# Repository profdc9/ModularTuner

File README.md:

This a project to create a Modular Antenna Tuner System that can be reconfigured for
different needs.  This material is copyrighted by Daniel Marks (KW4TI) and licensed under
the Creative Commons License CC-BY-SA 4.0.

This project is a toolkit for making automatic antenna tuners and smart HF antennas.

A description and documentation of this project may be found in the "doc" directory as
ModularTuner-Guide.pdf.

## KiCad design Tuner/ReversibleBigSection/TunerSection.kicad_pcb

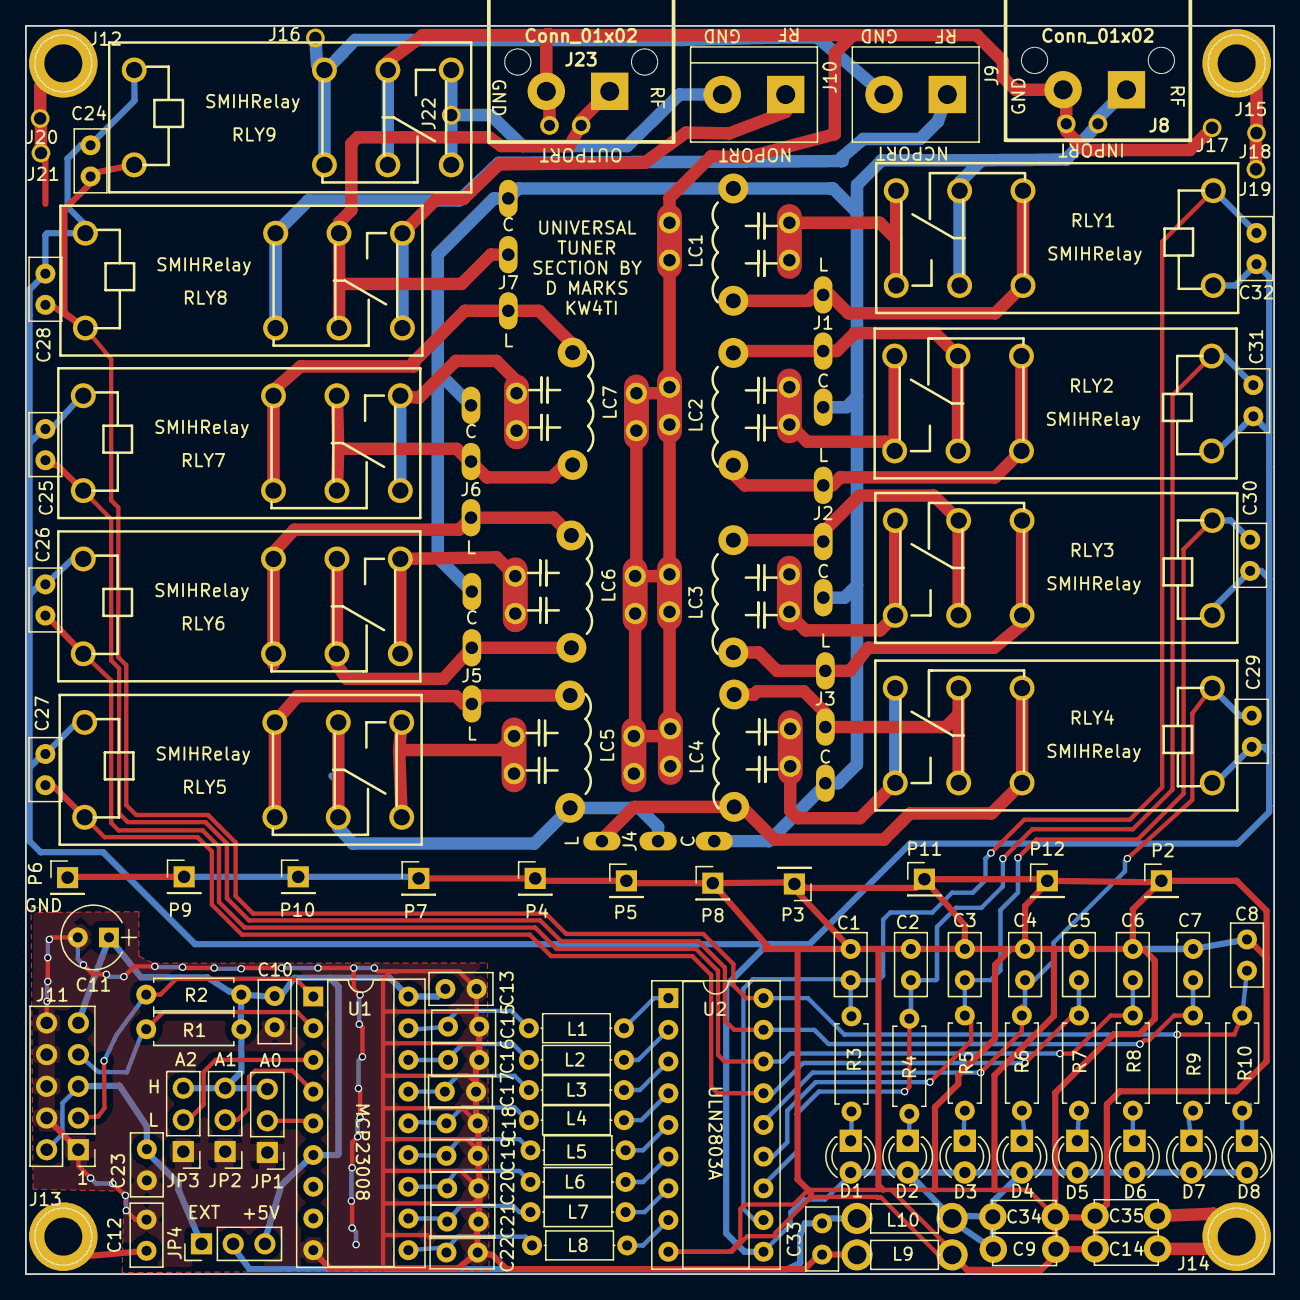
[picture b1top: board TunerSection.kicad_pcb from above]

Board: 2 copper layers, 100.0 x 100.0 mm, 119 parts (0 on the bottom side), 74 nets.

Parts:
C1, C2, C3, C4, C5, C6, C7, C8, C12, C15, C18, C19, C20, C21, C24, C25, C26, C27, C28, C29, C30, C31, C32: 10 nF; C_Disc_D5.0mm_W2.5mm_P2.50mm
C9, C14, C34, C35: 10 nF; C_Disc_D5.0mm_W2.5mm_P5.00mm
C10, C13, C23, C33: 100 nF; C_Disc_D5.0mm_W2.5mm_P2.50mm
C11: 100 uF; CP_Radial_Tantal_D5.0mm_P2.50mm
C16, C17: C_Small; C_Disc_D5.0mm_W2.5mm_P2.50mm
C22: 10 nFl; C_Disc_D5.0mm_W2.5mm_P2.50mm
D1, D2, D3, D4, D5, D6, D7, D8: LED; LED_D3.0mm
J1, J2, J3, J4, J5, J6, J7: Conn_01x03; ThreeJumperPt
J8, J23: Conn_01x02; bnc_90_1-1337543-0_pad_combo
J9, J10: Conn_01x02; TerminalBlock_bornier-2_P5.08mm
J11: Conn_02x05_Odd_Even; Pin_Header_Straight_2x05_Pitch2.54mm
J12, J13, J14, J15: Conn_01x01; 1pin
J16, J17, J18, J19, J20, J21, J22: Conn_01x01; SOLDERJUMPER
JP1, JP2, JP3, JP4: Jumper_NC_Dual; Pin_Header_Straight_1x03_Pitch2.54mm
L1, L2, L3, L4, L5, L6, L7, L8, L9, L10: 100 uH; L_Axial_L5.3mm_D2.2mm_P7.62mm_Horizontal_Vishay_IM-1
LC1, LC2, LC3, LC4, LC5, LC6, LC7: CAPIND; MultiCAPIND
P2, P3, P4, P5, P6, P7, P8, P9, P10, P11, P12: Conn_01x01; Pin_Header_Straight_1x01_Pitch2.54mm
R1, R2: 2.2k; R_Axial_DIN0207_L6.3mm_D2.5mm_P7.62mm_Horizontal
R3, R4, R5, R6, R7, R8, R9, R10: 1k; R_Axial_DIN0207_L6.3mm_D2.5mm_P7.62mm_Horizontal
RLY1, RLY2, RLY3, RLY4, RLY5, RLY6, RLY7, RLY8, RLY9: SPDTRelay; SMIHRelay
U1: MCP23008; DIP-18_W7.62mm_Socket
U2: ULN2803A; DIP-18_W7.62mm_Socket

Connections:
+5V: C10.2, C11.1, C13.2, J11.9, JP1.3, JP2.3, JP3.3, JP4.3, R1.1, R2.1, U1.6, U1.18
EXTPWR: C33.2, JP4.2, L10.1
GND: C10.1, C11.2, C12.2, C13.1, C15.2, C16.2, C17.2, C18.2, C19.2, C20.2, C21.2, C22.2, C23.1, C33.1, J11.1, J11.4, J11.6, J11.8, J11.10, JP1.1, JP2.1, JP3.1, L9.1, U1.9
unnamed: C12.1, J13.1
unnamed: C14.1, C35.1, J14.1
unnamed: C15.1, L1.1, U1.17
unnamed: C16.1, L2.1, U1.16
unnamed: C17.1, L3.1, U1.15
unnamed: C18.1, L4.1, U1.14
unnamed: C19.1, L5.1, U1.13
unnamed: C20.1, L6.1, U1.12
unnamed: C21.1, L7.1, U1.11
unnamed: C22.1, L8.1, U1.10
unnamed: C23.2, J11.2, J11.5, JP4.1
unnamed: D1.1, R3.1
unnamed: D2.1, R4.1
unnamed: D3.1, R5.1
unnamed: D4.1, R6.1
unnamed: D5.1, R7.1
unnamed: D6.1, R8.1
unnamed: D7.1, R9.1
unnamed: D8.1, R10.1
unnamed: J1.1, LC1.3, RLY1.2
unnamed: J1.2, LC2.4, RLY2.1
unnamed: J2.1, LC2.3, RLY2.2
unnamed: J2.2, LC3.4, RLY3.1
unnamed: J3.1, LC3.3, RLY3.2
unnamed: J3.2, LC4.4, RLY4.1
unnamed: J4.1, LC4.3, RLY4.2
unnamed: J4.2, LC5.4, RLY5.1
unnamed: J5.1, LC5.3, RLY5.2
unnamed: J5.2, LC6.4, RLY6.1
unnamed: J6.1, LC6.3, RLY6.2
unnamed: J6.2, LC7.4, RLY7.1
unnamed: J7.1, LC7.3, RLY7.2
unnamed: J9.1, RLY8.2
unnamed: J10.1, RLY8.3
unnamed: J10.2, J22.1, RLY9.3
unnamed: J12.1, J20.1, J21.1
unnamed: J15.1, J18.1, J19.1
unnamed: J9.2, J16.1, RLY9.2
unnamed: J7.2, J23.1, RLY8.1
unnamed: JP1.2, U1.5
unnamed: JP2.2, U1.4
unnamed: JP3.2, U1.3
unnamed: L1.2, U2.1
unnamed: L2.2, U2.2
unnamed: L3.2, U2.3
unnamed: L4.2, U2.4
unnamed: L5.2, U2.5
unnamed: L6.2, U2.6
unnamed: L7.2, U2.7
unnamed: L8.2, U2.8
unnamed: LC1.1, RLY1.3
unnamed: LC2.1, RLY2.3
unnamed: LC3.1, RLY3.3
unnamed: LC4.1, RLY4.3
unnamed: LC5.1, RLY5.3
unnamed: LC6.1, RLY6.3
unnamed: LC7.1, RLY7.3
RFGND: J8.2, J17.1, J23.2, LC1.2, LC2.2, LC3.2, LC4.2, LC5.2, LC6.2, LC7.2, RLY9.1
RFPORT1: J1.3, J2.3, J3.3, J4.3, J5.3, J6.3, J7.3, J8.1, LC1.4, RLY1.1
RLY1: C1.2, C32.2, R3.2, RLY1.5, U2.11
RLY2: C2.2, C31.2, R4.2, RLY2.5, U2.12
RLY3: C3.2, C30.2, R5.2, RLY3.5, U2.13
RLY4: C4.2, C29.2, R6.2, RLY4.5, U2.14
RLY5: C5.2, C27.2, R7.2, RLY5.5, U2.15
RLY6: C6.2, C26.2, R8.2, RLY6.5, U2.16
RLY7: C7.2, C25.2, R9.2, RLY7.5, U2.17
RLY8: C8.2, C24.2, C28.2, R10.2, RLY8.5, RLY9.5, U2.18
RLYGND: C1.1, C2.1, C3.1, C4.1, C5.1, C6.1, C7.1, C8.1, C9.2, C14.2, C34.2, C35.2, L9.2, P2.1, P3.1, P4.1, P5.1, P6.1, P7.1, P8.1, P9.1, P10.1, P11.1, P12.1, U2.9
RLYPWR: C9.1, C24.1, C25.1, C26.1, C27.1, C28.1, C29.1, C30.1, C31.1, C32.1, C34.1, D1.2, D2.2, D3.2, D4.2, D5.2, D6.2, D7.2, D8.2, L10.2, RLY1.4, RLY2.4, RLY3.4, RLY4.4, RLY5.4, RLY6.4, RLY7.4, RLY8.4, RLY9.4, U2.10
SCL: J11.3, R2.2, U1.1
SDA: J11.7, R1.2, U1.2

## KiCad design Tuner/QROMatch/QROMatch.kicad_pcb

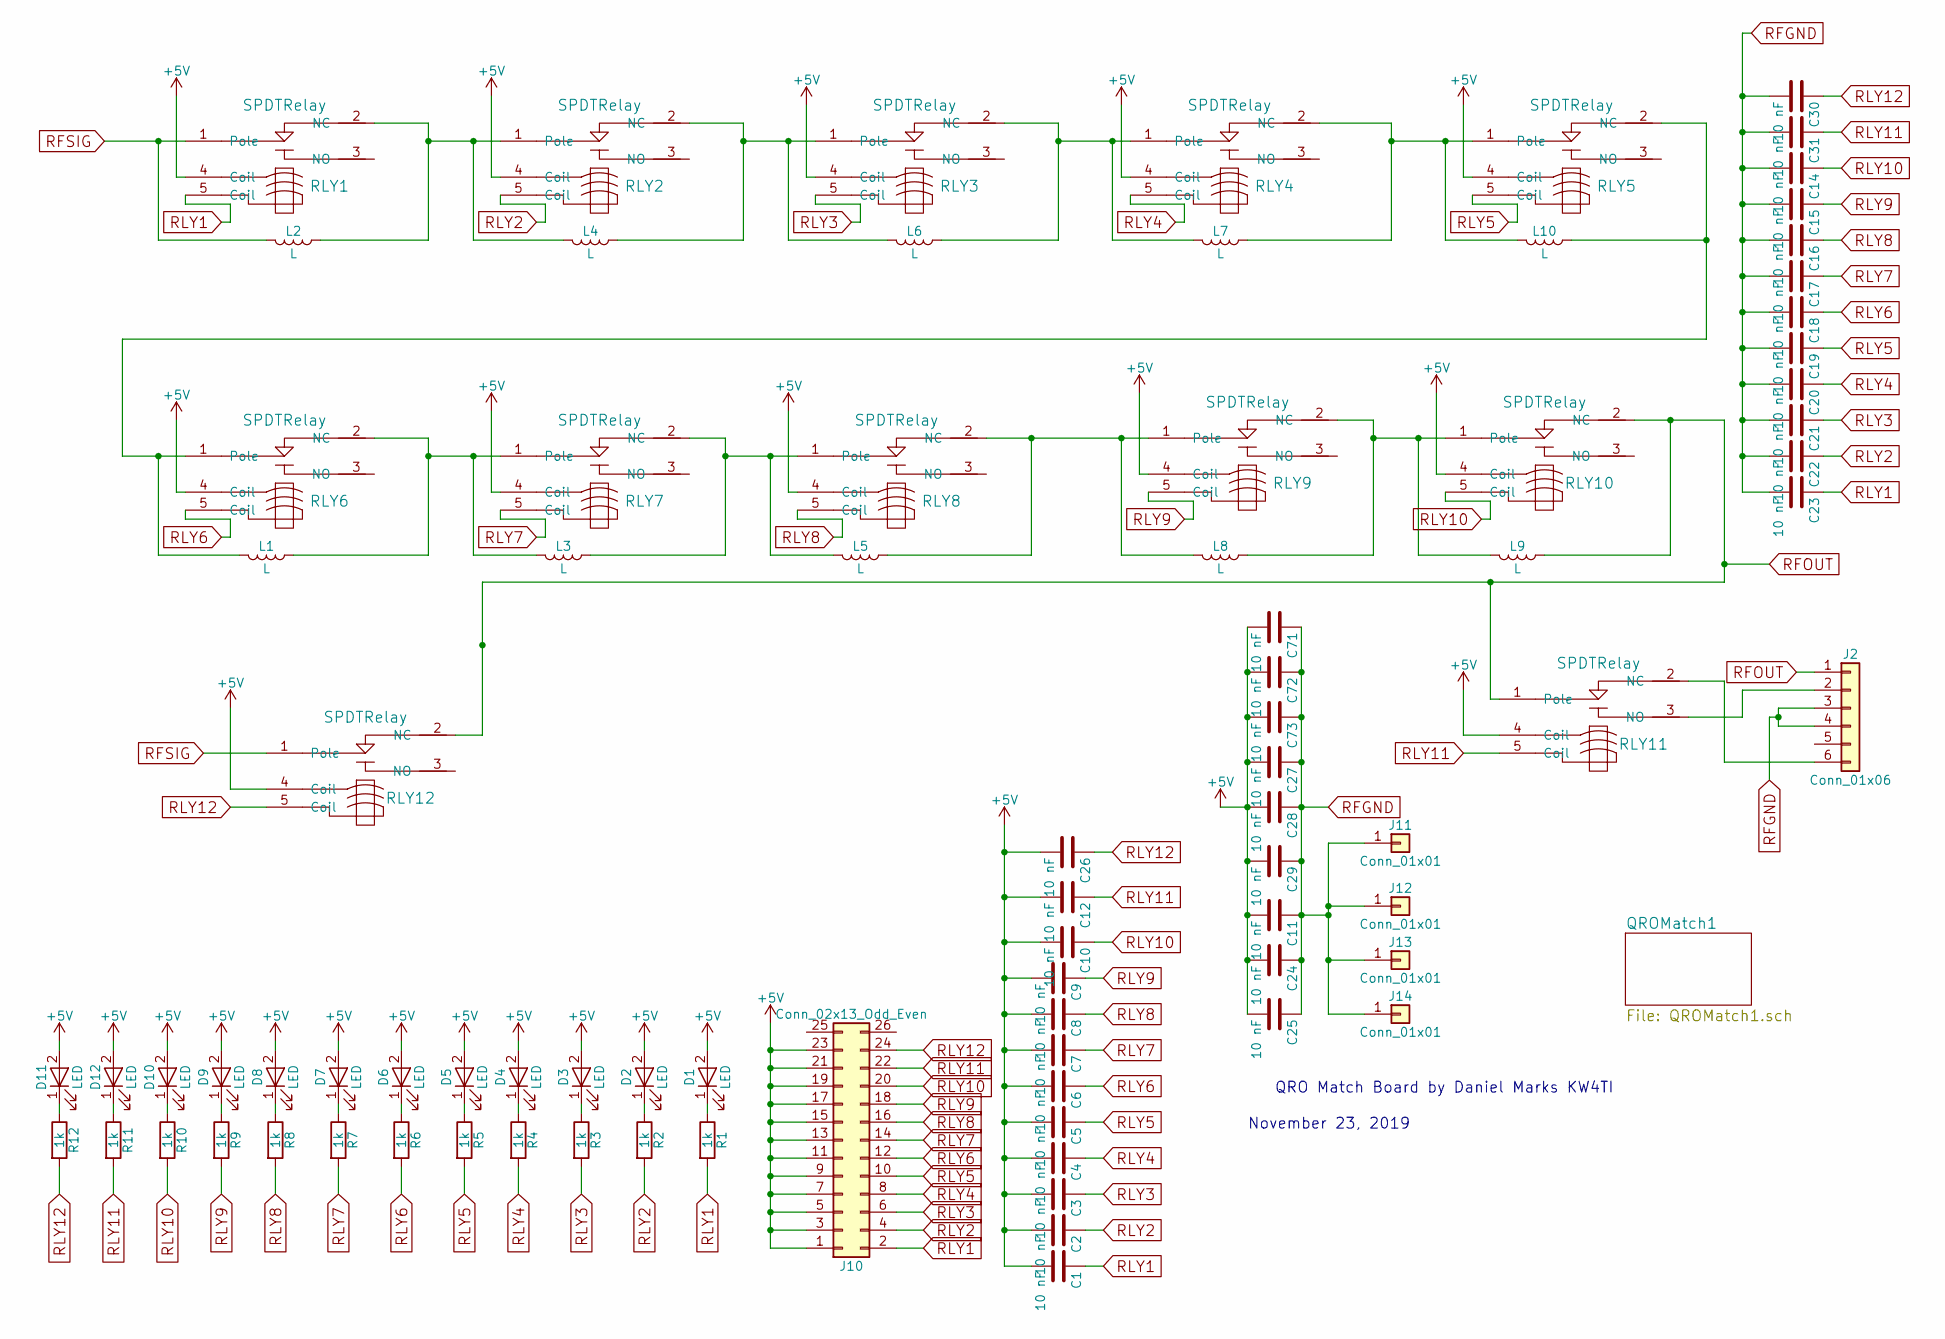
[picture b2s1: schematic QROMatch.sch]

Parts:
C1, C2, C3, C4, C5, C6, C7, C8, C9, C10, C12, C14, C15, C16, C17, C18, C19, C20, C21, C22, C23, C26, C27, C28, C29, C30, C31, C71, C72, C73: 10 nF; C_Disc_D5.0mm_W2.5mm_P2.50mm
C11, C24, C25: 10 nF; C_Disc_D5.0mm_W2.5mm_P5.00mm
D1, D2, D3, D4, D5, D6, D7, D8, D9, D10, D11, D12: LED; LED_D3.0mm
J2: Conn_01x06; TerminalBlock_bornier-6_P5.08mm
J10: Conn_02x13_Odd_Even; Pin_Header_Straight_2x13_Pitch2.54mm
J11, J12, J13, J14: Conn_01x01; 1pin
L1, L2, L3, L4, L5, L6, L7, L8, L9, L10: L; InductorPad
R1, R2, R3, R4, R5, R6, R7, R8, R9, R10, R11, R12: 1k; R_Axial_DIN0207_L6.3mm_D2.5mm_P7.62mm_Horizontal
RLY1, RLY2, RLY3, RLY4, RLY5, RLY6, RLY7, RLY8, RLY9, RLY10, RLY11, RLY12: SPDTRelay; SMIHRelay

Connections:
+5V: C1.2, C2.2, C3.2, C4.2, C5.2, C6.2, C7.2, C8.2, C9.2, C10.2, C11.2, C12.2, C24.2, C25.2, C26.2, C27.2, C28.2, C29.2, C71.2, C72.2, C73.2, D1.2 (A), D2.2 (A), D3.2 (A), D4.2 (A), D5.2 (A), D6.2 (A), D7.2 (A), D8.2 (A), D9.2 (A), D10.2 (A), D11.2 (A), D12.2 (A), J10.1, J10.3, J10.5, J10.7, J10.9, J10.11, J10.13, J10.15, J10.17, J10.19, J10.21, J10.23, RLY1.4 (Coil), RLY2.4 (Coil), RLY3.4 (Coil), RLY4.4 (Coil), RLY5.4 (Coil), RLY6.4 (Coil), RLY7.4 (Coil), RLY8.4 (Coil), RLY9.4 (Coil), RLY10.4 (Coil), RLY11.4 (Coil), RLY12.4 (Coil)
unnamed: D1.1 (K), R1.1
unnamed: D2.1 (K), R2.1
unnamed: D3.1 (K), R3.1
unnamed: D4.1 (K), R4.1
unnamed: D5.1 (K), R5.1
unnamed: D6.1 (K), R6.1
unnamed: D7.1 (K), R7.1
unnamed: D8.1 (K), R8.1
unnamed: D9.1 (K), R9.1
unnamed: D10.1 (K), R10.1
unnamed: D11.1 (K), R12.1
unnamed: D12.1 (K), R11.1
unnamed: J2.2, RLY11.3 (NO)
unnamed: J2.6, RLY11.2 (NC)
unnamed: L1.1, L3.2, RLY6.2 (NC), RLY7.1 (Pole)
unnamed: L1.2, L10.1, RLY5.2 (NC), RLY6.1 (Pole)
unnamed: L2.1, L4.2, RLY1.2 (NC), RLY2.1 (Pole)
unnamed: L3.1, L5.2, RLY7.2 (NC), RLY8.1 (Pole)
unnamed: L4.1, L6.2, RLY2.2 (NC), RLY3.1 (Pole)
unnamed: L5.1, L8.2, RLY8.2 (NC), RLY9.1 (Pole)
unnamed: L6.1, L7.2, RLY3.2 (NC), RLY4.1 (Pole)
unnamed: L8.1, L9.2, RLY9.2 (NC), RLY10.1 (Pole)
unnamed: L7.1, L10.2, RLY4.2 (NC), RLY5.1 (Pole)
RFGND: C11.1, C14.2, C15.2, C16.2, C17.2, C18.2, C19.2, C20.2, C21.2, C22.2, C23.2, C24.1, C25.1, C27.1, C28.1, C29.1, C30.2, C31.2, C71.1, C72.1, C73.1, J2.3, J2.4, J11.1, J12.1, J13.1, J14.1; also elsewhere on the board
RFOUT: J2.1, L9.1, RLY10.2 (NC), RLY11.1 (Pole), RLY12.2 (NC); also elsewhere on the board
RFSIG: L2.2, RLY1.1 (Pole), RLY12.1 (Pole); also elsewhere on the board
RLY1: C1.1, C23.1, J10.2, R1.2, RLY1.5 (Coil)
RLY2: C2.1, C22.1, J10.4, R2.2, RLY2.5 (Coil)
RLY3: C3.1, C21.1, J10.6, R3.2, RLY3.5 (Coil)
RLY4: C4.1, C20.1, J10.8, R4.2, RLY4.5 (Coil)
RLY5: C5.1, C19.1, J10.10, R5.2, RLY5.5 (Coil)
RLY6: C6.1, C18.1, J10.12, R6.2, RLY6.5 (Coil)
RLY7: C7.1, C17.1, J10.14, R7.2, RLY7.5 (Coil)
RLY8: C8.1, C16.1, J10.16, R8.2, RLY8.5 (Coil)
RLY9: C9.1, C15.1, J10.18, R9.2, RLY9.5 (Coil)
RLY10: C10.1, C14.1, J10.20, R10.2, RLY10.5 (Coil)
RLY11: C12.1, C31.1, J10.22, R11.2, RLY11.5 (Coil)
RLY12: C26.1, C30.1, J10.24, R12.2, RLY12.5 (Coil)

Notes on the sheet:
QRO Match Board by Daniel Marks KW4TI
November 23, 2019

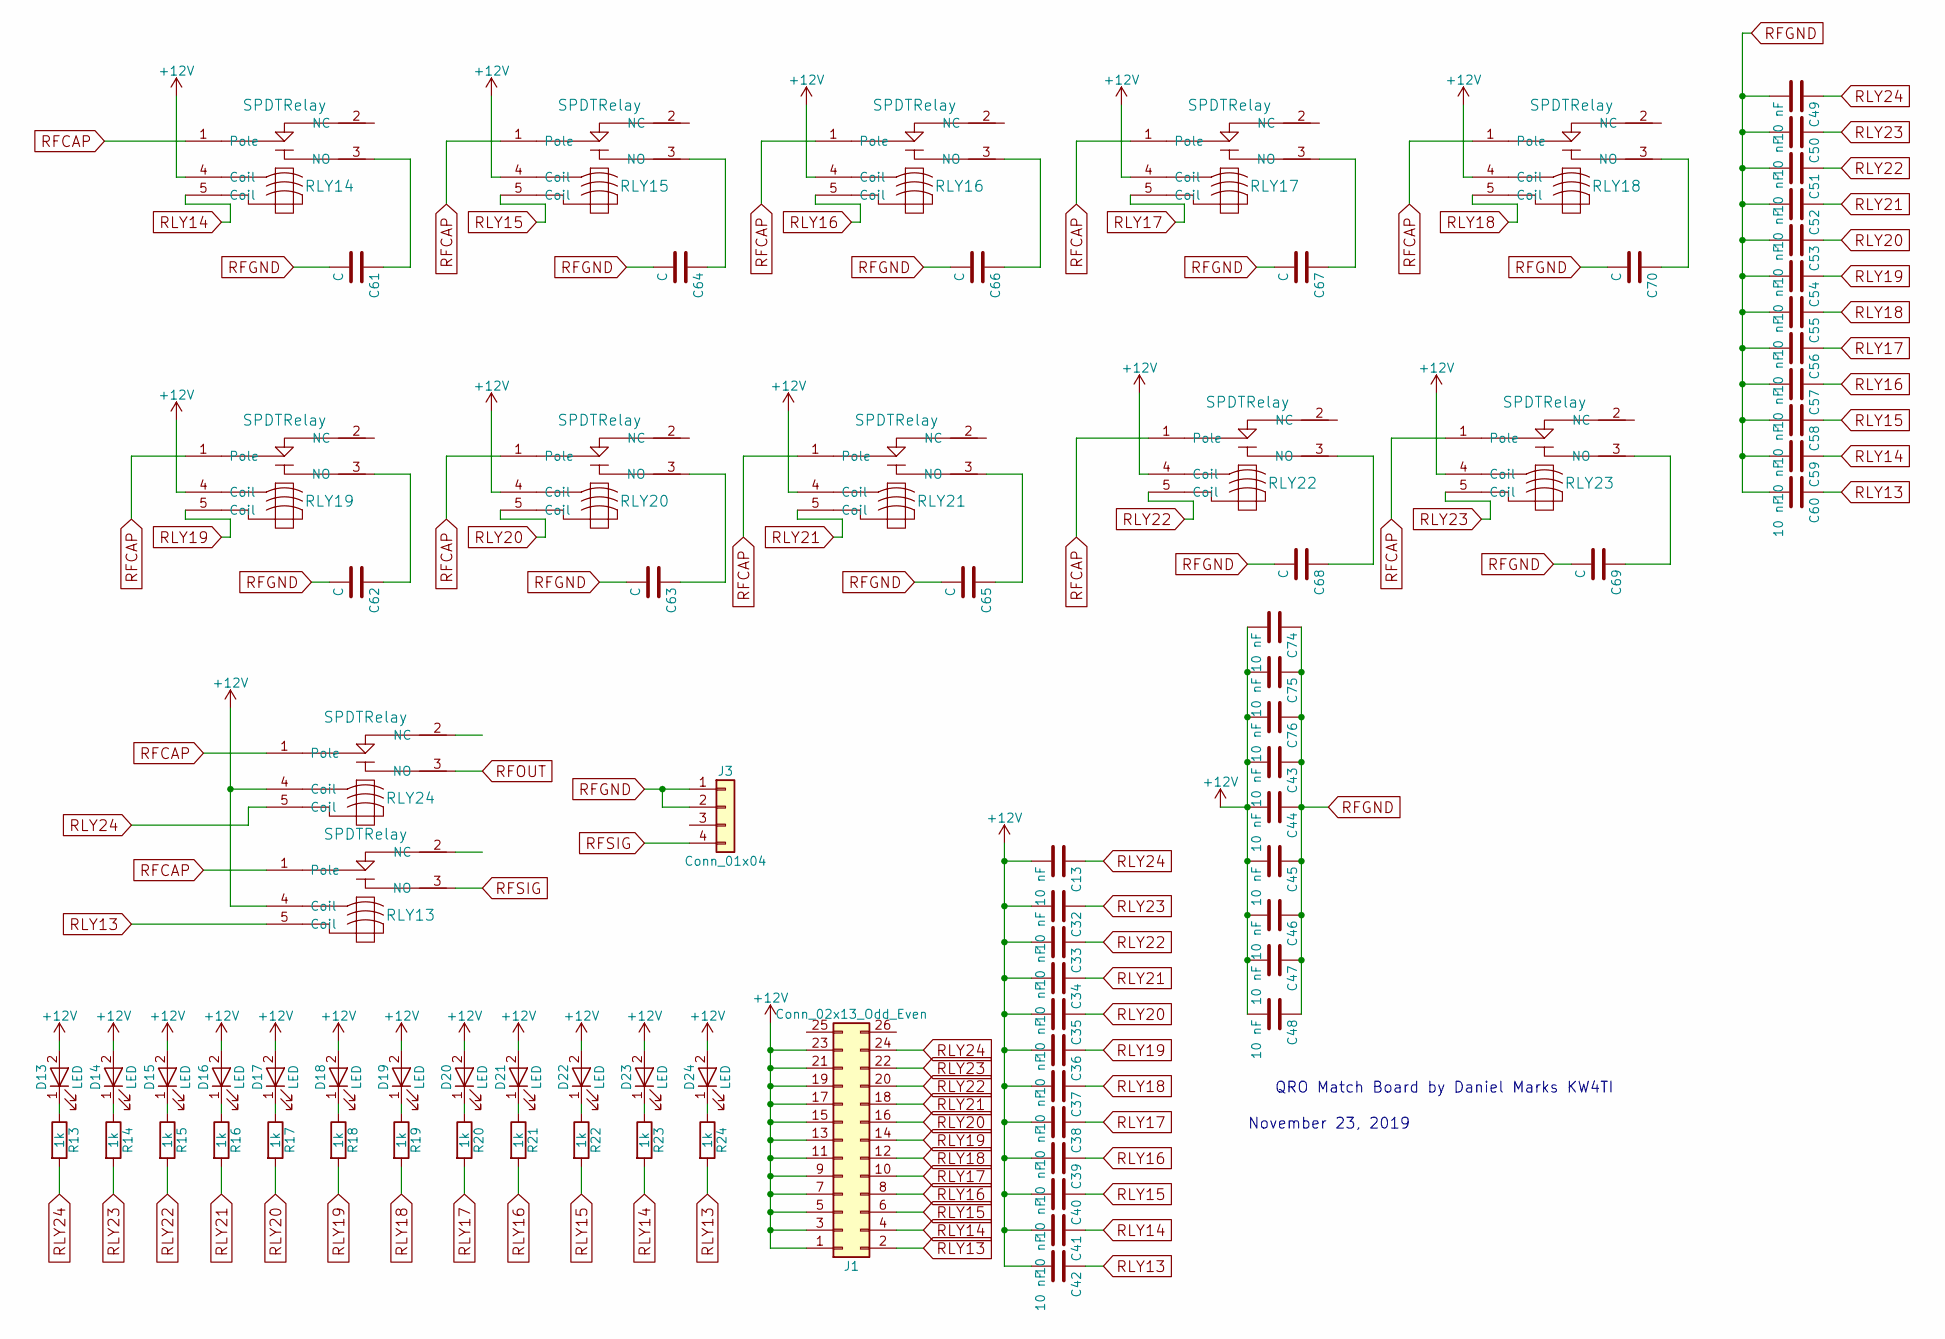
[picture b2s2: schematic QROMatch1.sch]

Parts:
C13, C32, C33, C34, C35, C36, C37, C38, C39, C40, C41, C42, C43, C44, C45, C49, C50, C51, C52, C53, C54, C55, C56, C57, C58, C59, C60, C74, C75, C76: 10 nF; C_Disc_D5.0mm_W2.5mm_P2.50mm
C46, C47, C48: 10 nF; C_Disc_D5.0mm_W2.5mm_P5.00mm
C61, C62, C63, C64, C65, C66, C67, C68, C69, C70: C; CapacitorPad
D13, D14, D15, D16, D17, D18, D19, D20, D21, D22, D23, D24: LED; LED_D3.0mm
J1: Conn_02x13_Odd_Even; Pin_Header_Straight_2x13_Pitch2.54mm
J3: Conn_01x04; TerminalBlock_bornier-4_P5.08mm
R13, R14, R15, R16, R17, R18, R19, R20, R21, R22, R23, R24: 1k; R_Axial_DIN0207_L6.3mm_D2.5mm_P7.62mm_Horizontal
RLY13, RLY14, RLY15, RLY16, RLY17, RLY18, RLY19, RLY20, RLY21, RLY22, RLY23, RLY24: SPDTRelay; SMIHRelay

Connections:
+12V: C13.2, C32.2, C33.2, C34.2, C35.2, C36.2, C37.2, C38.2, C39.2, C40.2, C41.2, C42.2, C43.2, C44.2, C45.2, C46.2, C47.2, C48.2, C74.2, C75.2, C76.2, D13.2 (A), D14.2 (A), D15.2 (A), D16.2 (A), D17.2 (A), D18.2 (A), D19.2 (A), D20.2 (A), D21.2 (A), D22.2 (A), D23.2 (A), D24.2 (A), J1.1, J1.3, J1.5, J1.7, J1.9, J1.11, J1.13, J1.15, J1.17, J1.19, J1.21, J1.23, RLY13.4 (Coil), RLY14.4 (Coil), RLY15.4 (Coil), RLY16.4 (Coil), RLY17.4 (Coil), RLY18.4 (Coil), RLY19.4 (Coil), RLY20.4 (Coil), RLY21.4 (Coil), RLY22.4 (Coil), RLY23.4 (Coil), RLY24.4 (Coil)
unnamed: C61.1, RLY14.3 (NO)
unnamed: C62.1, RLY19.3 (NO)
unnamed: C63.1, RLY20.3 (NO)
unnamed: C64.1, RLY15.3 (NO)
unnamed: C65.1, RLY21.3 (NO)
unnamed: C66.1, RLY16.3 (NO)
unnamed: C67.1, RLY17.3 (NO)
unnamed: C68.1, RLY22.3 (NO)
unnamed: C69.1, RLY23.3 (NO)
unnamed: C70.1, RLY18.3 (NO)
unnamed: D13.1 (K), R13.1
unnamed: D14.1 (K), R14.1
unnamed: D15.1 (K), R15.1
unnamed: D16.1 (K), R16.1
unnamed: D17.1 (K), R17.1
unnamed: D18.1 (K), R18.1
unnamed: D19.1 (K), R19.1
unnamed: D20.1 (K), R20.1
unnamed: D21.1 (K), R21.1
unnamed: D22.1 (K), R22.1
unnamed: D23.1 (K), R23.1
unnamed: D24.1 (K), R24.1
RFCAP: RLY13.1 (Pole), RLY14.1 (Pole), RLY15.1 (Pole), RLY16.1 (Pole), RLY17.1 (Pole), RLY18.1 (Pole), RLY19.1 (Pole), RLY20.1 (Pole), RLY21.1 (Pole), RLY22.1 (Pole), RLY23.1 (Pole), RLY24.1 (Pole)
RFGND: C43.1, C44.1, C45.1, C46.1, C47.1, C48.1, C49.2, C50.2, C51.2, C52.2, C53.2, C54.2, C55.2, C56.2, C57.2, C58.2, C59.2, C60.2, C61.2, C62.2, C63.2, C64.2, C65.2, C66.2, C67.2, C68.2, C69.2, C70.2, C74.1, C75.1, C76.1, J3.1, J3.2; also elsewhere on the board
RFOUT: RLY24.3 (NO); also elsewhere on the board
RFSIG: J3.4, RLY13.3 (NO); also elsewhere on the board
RLY13: C42.1, C60.1, J1.2, R24.2, RLY13.5 (Coil)
RLY14: C41.1, C59.1, J1.4, R23.2, RLY14.5 (Coil)
RLY15: C40.1, C58.1, J1.6, R22.2, RLY15.5 (Coil)
RLY16: C39.1, C57.1, J1.8, R21.2, RLY16.5 (Coil)
RLY17: C38.1, C56.1, J1.10, R20.2, RLY17.5 (Coil)
RLY18: C37.1, C55.1, J1.12, R19.2, RLY18.5 (Coil)
RLY19: C36.1, C54.1, J1.14, R18.2, RLY19.5 (Coil)
RLY20: C35.1, C53.1, J1.16, R17.2, RLY20.5 (Coil)
RLY21: C34.1, C52.1, J1.18, R16.2, RLY21.5 (Coil)
RLY22: C33.1, C51.1, J1.20, R15.2, RLY22.5 (Coil)
RLY23: C32.1, C50.1, J1.22, R14.2, RLY23.5 (Coil)
RLY24: C13.1, C49.1, J1.24, R13.2, RLY24.5 (Coil)

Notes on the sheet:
QRO Match Board by Daniel Marks KW4TI
November 23, 2019

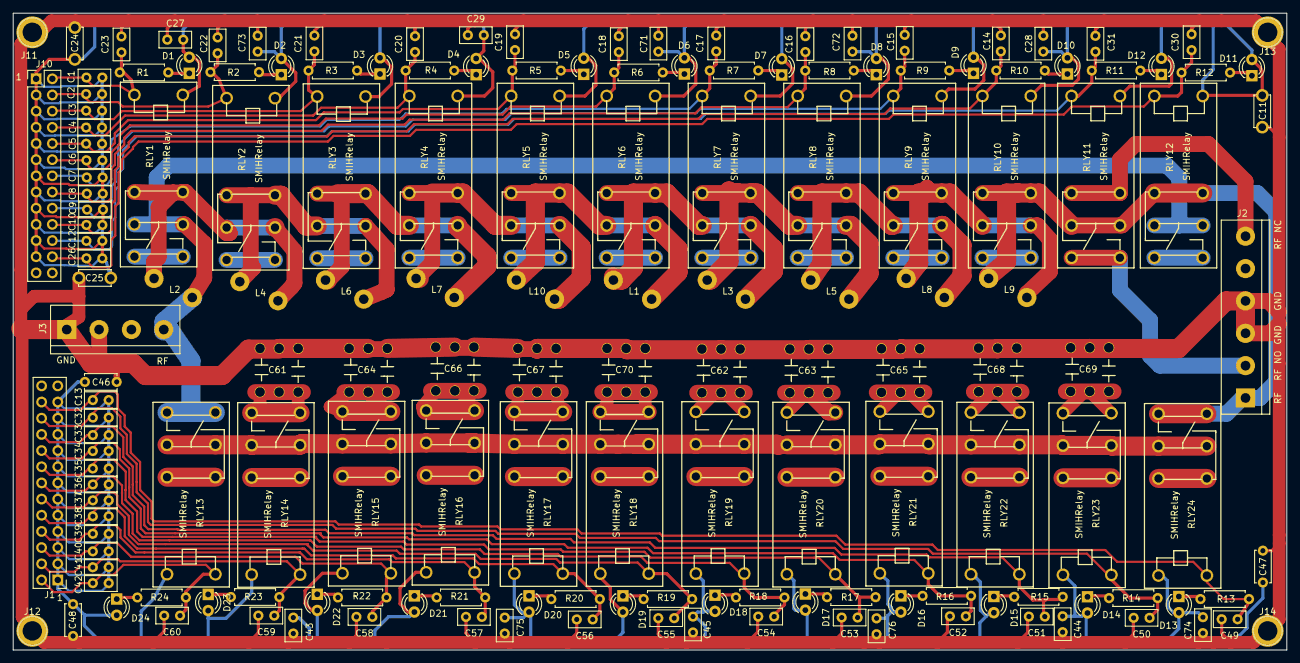
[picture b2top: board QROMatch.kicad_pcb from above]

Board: 2 copper layers, 200.0 x 100.0 mm, 166 parts (0 on the bottom side), 75 nets.

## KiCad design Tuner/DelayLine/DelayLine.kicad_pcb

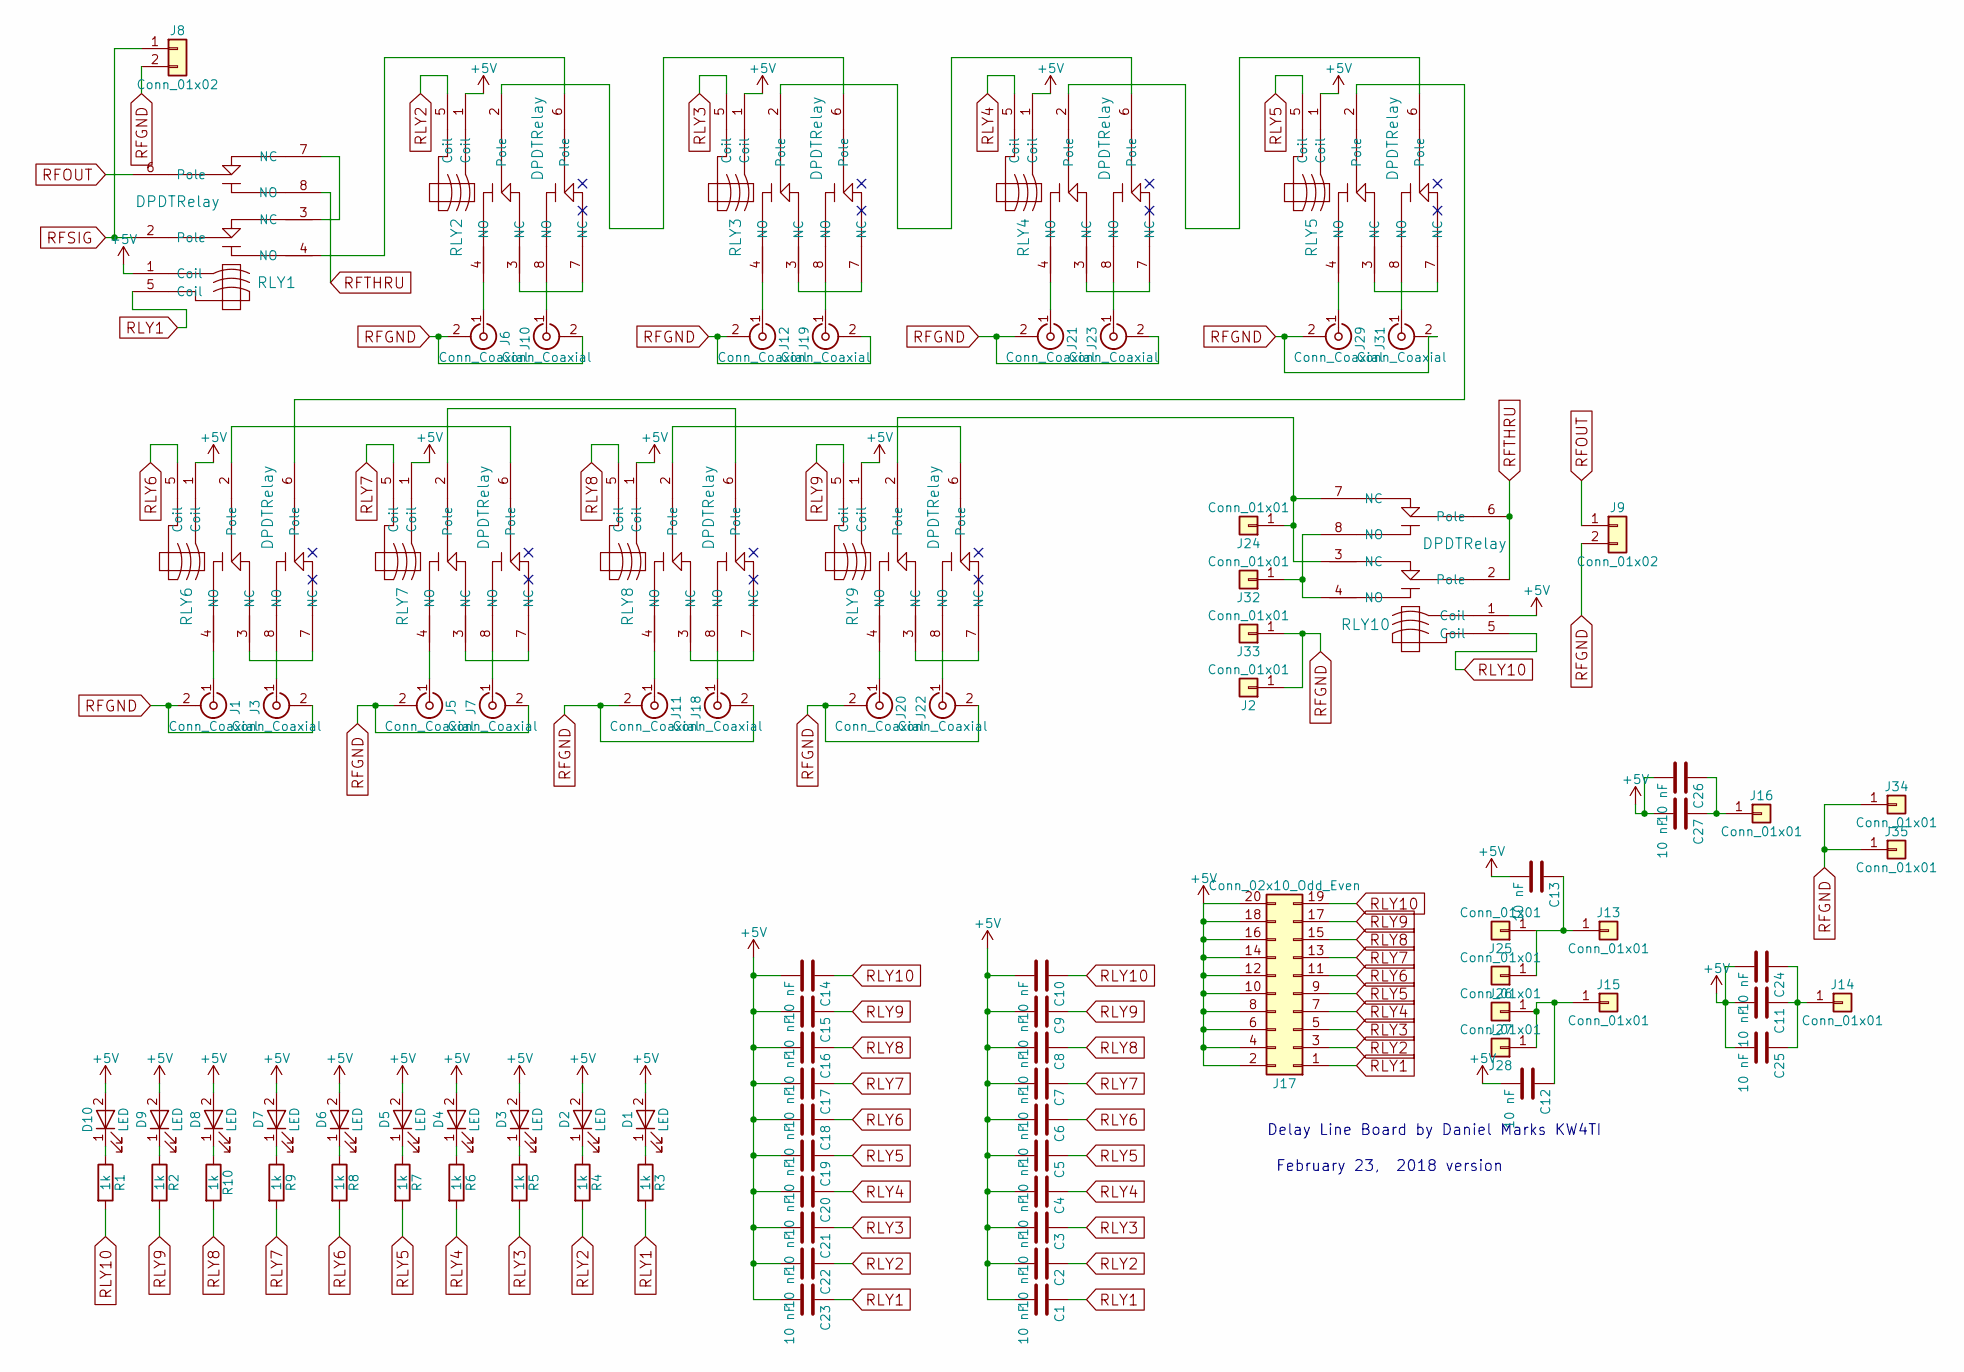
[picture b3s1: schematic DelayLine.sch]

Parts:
C1, C2, C3, C4, C5, C6, C7, C8, C9, C10, C12, C13, C14, C15, C16, C17, C18, C19, C20, C21, C22, C23: 10 nF; C_Disc_D5.0mm_W2.5mm_P2.50mm
C11, C24, C25, C26, C27: 10 nF; C_Disc_D5.0mm_W2.5mm_P5.00mm
D1, D2, D3, D4, D5, D6, D7, D8, D9, D10: LED; LED_D3.0mm
J1, J3, J5, J6, J7, J10, J11, J12, J18, J19, J20, J21, J22, J23, J29, J31: Conn_Coaxial; bnc-ci
J2, J13, J14, J15, J16, J24, J32, J33: Conn_01x01; 1pin
J8, J9: Conn_01x02; bnc_90_1-1337543-0_pad_combo
J17: Conn_02x10_Odd_Even; Pin_Header_Straight_2x10_Pitch2.54mm
J25, J26, J27, J28, J34, J35: Conn_01x01; SOLDERJUMPER
R1, R2, R3, R4, R5, R6, R7, R8, R9, R10: 1k; R_Axial_DIN0207_L6.3mm_D2.5mm_P7.62mm_Horizontal
RLY1, RLY2, RLY3, RLY4, RLY5, RLY6, RLY7, RLY8, RLY9, RLY10: DPDTRelay; G2VRelay

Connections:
+5V: C1.2, C2.2, C3.2, C4.2, C5.2, C6.2, C7.2, C8.2, C9.2, C10.2, C11.2, C12.2, C13.2, C14.2, C15.2, C16.2, C17.2, C18.2, C19.2, C20.2, C21.2, C22.2, C23.2, C24.2, C25.2, C26.2, C27.2, D1.2 (A), D2.2 (A), D3.2 (A), D4.2 (A), D5.2 (A), D6.2 (A), D7.2 (A), D8.2 (A), D9.2 (A), D10.2 (A), J17.2, J17.4, J17.6, J17.8, J17.10, J17.12, J17.14, J17.16, J17.18, J17.20, RLY1.1 (Coil), RLY2.1 (Coil), RLY3.1 (Coil), RLY4.1 (Coil), RLY5.1 (Coil), RLY6.1 (Coil), RLY7.1 (Coil), RLY8.1 (Coil), RLY9.1 (Coil), RLY10.1 (Coil)
unnamed: C11.1, C24.1, C25.1, J14.1
unnamed: C12.1, J15.1, J27.1, J28.1
unnamed: C13.1, J13.1, J25.1, J26.1
unnamed: C26.1, C27.1, J16.1
unnamed: D1.1 (K), R3.1
unnamed: D2.1 (K), R4.1
unnamed: D3.1 (K), R5.1
unnamed: D4.1 (K), R6.1
unnamed: D5.1 (K), R7.1
unnamed: D6.1 (K), R8.1
unnamed: D7.1 (K), R9.1
unnamed: D8.1 (K), R10.1
unnamed: D9.1 (K), R2.1
unnamed: D10.1 (K), R1.1
unnamed: J1.1 (In), RLY6.4 (NO)
unnamed: J3.1 (In), RLY6.8 (NO)
unnamed: J5.1 (In), RLY7.4 (NO)
unnamed: J6.1 (In), RLY2.4 (NO)
unnamed: J7.1 (In), RLY7.8 (NO)
unnamed: J10.1 (In), RLY2.8 (NO)
unnamed: J11.1 (In), RLY8.4 (NO)
unnamed: J12.1 (In), RLY3.4 (NO)
unnamed: J18.1 (In), RLY8.8 (NO)
unnamed: J19.1 (In), RLY3.8 (NO)
unnamed: J20.1 (In), RLY9.4 (NO)
unnamed: J21.1 (In), RLY4.4 (NO)
unnamed: J22.1 (In), RLY9.8 (NO)
unnamed: J23.1 (In), RLY4.8 (NO)
unnamed: J24.1, RLY9.2 (Pole), RLY10.3 (NC), RLY10.7 (NC)
unnamed: J29.1 (In), RLY5.4 (NO)
unnamed: J31.1 (In), RLY5.8 (NO)
unnamed: J32.1, RLY10.4 (NO), RLY10.8 (NO)
unnamed: RLY1.3 (NC), RLY1.7 (NC)
unnamed: RLY1.4 (NO), RLY2.6 (Pole)
unnamed: RLY2.2 (Pole), RLY3.6 (Pole)
unnamed: RLY2.3 (NC), RLY2.7 (NC)
unnamed: RLY3.2 (Pole), RLY4.6 (Pole)
unnamed: RLY3.3 (NC), RLY3.7 (NC)
unnamed: RLY4.2 (Pole), RLY5.6 (Pole)
unnamed: RLY4.3 (NC), RLY4.7 (NC)
unnamed: RLY5.2 (Pole), RLY6.6 (Pole)
unnamed: RLY5.3 (NC), RLY5.7 (NC)
unnamed: RLY6.2 (Pole), RLY7.6 (Pole)
unnamed: RLY6.3 (NC), RLY6.7 (NC)
unnamed: RLY7.2 (Pole), RLY8.6 (Pole)
unnamed: RLY7.3 (NC), RLY7.7 (NC)
unnamed: RLY8.2 (Pole), RLY9.6 (Pole)
unnamed: RLY8.3 (NC), RLY8.7 (NC)
unnamed: RLY9.3 (NC), RLY9.7 (NC)
RFGND: J1.2 (Ext), J2.1, J3.2 (Ext), J5.2 (Ext), J6.2 (Ext), J7.2 (Ext), J8.2, J9.2, J10.2 (Ext), J11.2 (Ext), J12.2 (Ext), J18.2 (Ext), J19.2 (Ext), J20.2 (Ext), J21.2 (Ext), J22.2 (Ext), J23.2 (Ext), J29.2 (Ext), J31.2 (Ext), J33.1, J34.1, J35.1
RFOUT: J9.1, RLY1.6 (Pole)
RFSIG: J8.1, RLY1.2 (Pole)
RFTHRU: RLY1.8 (NO), RLY10.2 (Pole), RLY10.6 (Pole)
RLY1: C1.1, C23.1, J17.1, R3.2, RLY1.5 (Coil)
RLY2: C2.1, C22.1, J17.3, R4.2, RLY2.5 (Coil)
RLY3: C3.1, C21.1, J17.5, R5.2, RLY3.5 (Coil)
RLY4: C4.1, C20.1, J17.7, R6.2, RLY4.5 (Coil)
RLY5: C5.1, C19.1, J17.9, R7.2, RLY5.5 (Coil)
RLY6: C6.1, C18.1, J17.11, R8.2, RLY6.5 (Coil)
RLY7: C7.1, C17.1, J17.13, R9.2, RLY7.5 (Coil)
RLY8: C8.1, C16.1, J17.15, R10.2, RLY8.5 (Coil)
RLY9: C9.1, C15.1, J17.17, R2.2, RLY9.5 (Coil)
RLY10: C10.1, C14.1, J17.19, R1.2, RLY10.5 (Coil)

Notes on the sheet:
Delay Line Board by Daniel Marks KW4TI
February 23, 2018 version

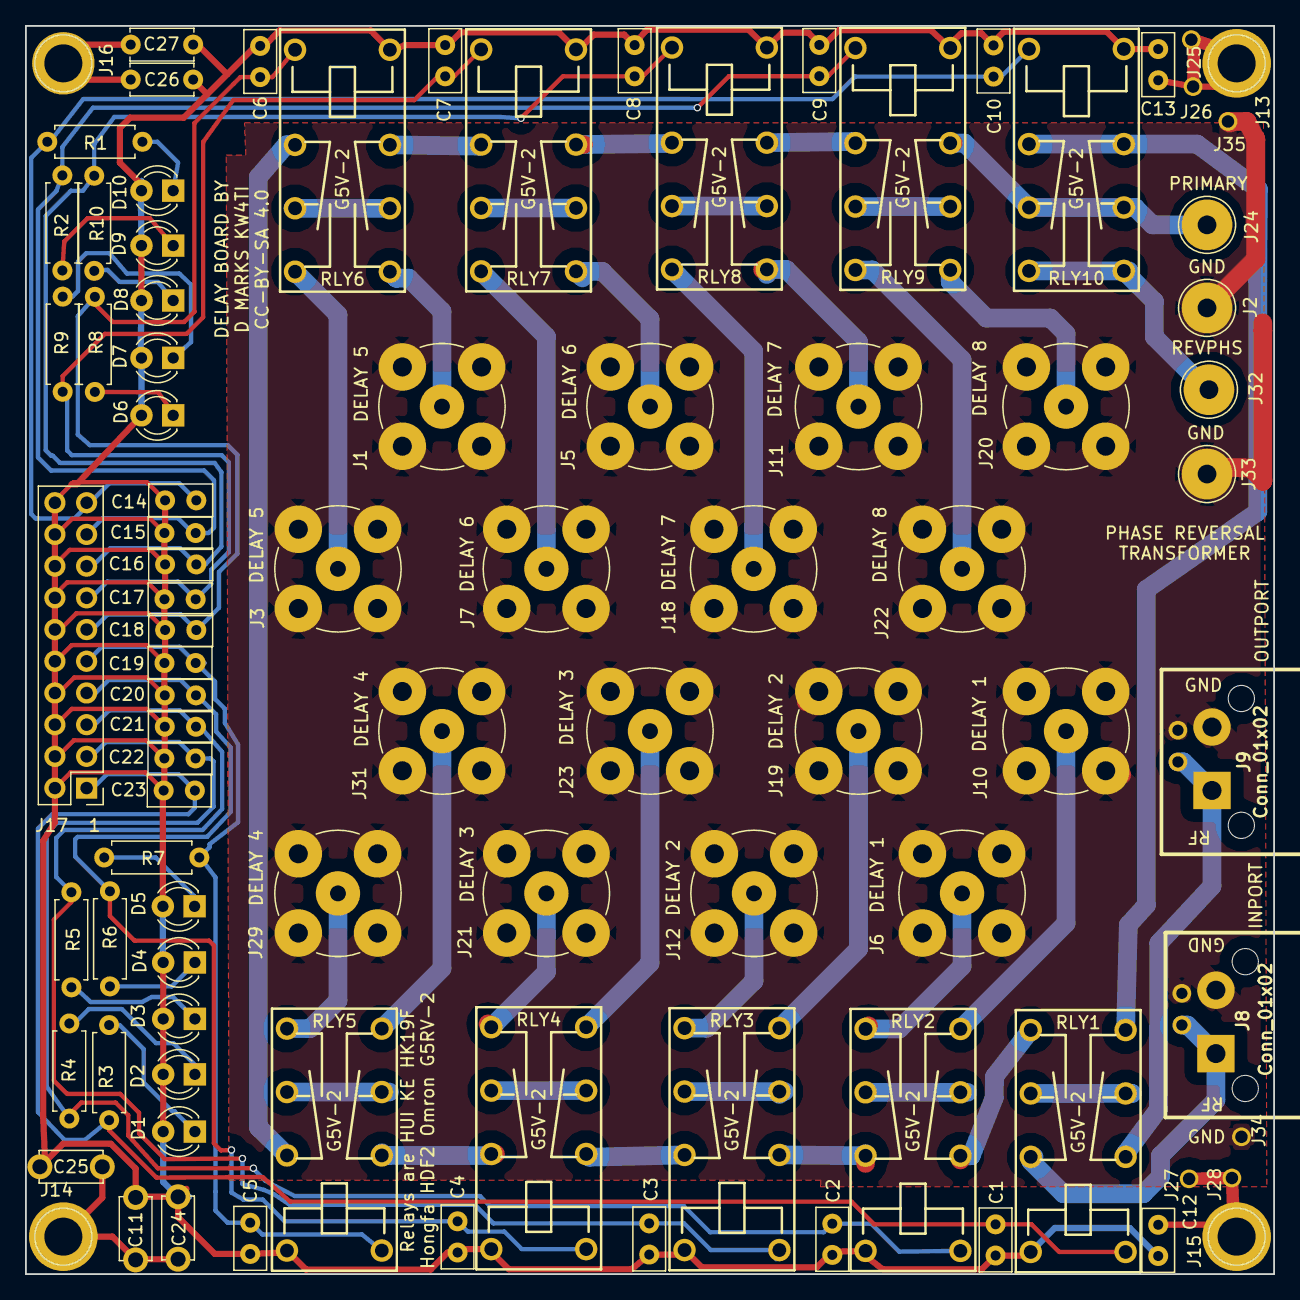
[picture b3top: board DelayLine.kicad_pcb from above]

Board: 2 copper layers, 100.0 x 100.0 mm, 90 parts (0 on the bottom side), 64 nets.
